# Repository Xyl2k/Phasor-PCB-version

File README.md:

# PHASOR AVR Demo — Custom PCB

This repository contains a custom double-layer PCB design for running the [PHASOR demo](https://www.linusakesson.net/hardware/phasor/index.php) by Linus Åkesson on an ATmega88-20PU microcontroller.

---

## 📁 Contents

- `JSON/`: EasyEDA schematic and board layout plus one 'swapped version' of the RCA connectors 
- `firmware/`: Precompiled HEX file and Flipper Zero-compatible firmware folder
- `enclosure/`: 3D enclosure model (`.stl`)
- `README.md`: Project documentation

---

## ⚙️ Features

- Pure AVR synth demo running on ATmega88  
- Composite PAL video output  
- Generative visuals synced to audio    
- 5V operation (via 78L05 regulator)  
- ISP programming header for flashing

---

## 📦 Bill of Materials (BOM)

| Qty | Component               | Specification           |
|-----|-------------------------|--------------------------|
| x1  | Resistor                | 220 Ω                    |
| x4  | Resistor                | 442 Ω                    |
| x11 | Resistor                | 1 kΩ                     |
| x19 | Resistor                | 2 kΩ                     |
| x3  | Diode                   | 1N4148-35                |
| x2  | Ceramic Capacitor       | 22 pF                    |
| x2  | Electrolytic Capacitor  | 10 µF                    |
| x1  | Header (SPI)            | 2x3                      |
| x1  | Header (Power)          | 1x2                      |
| x1  | LED                     | 3 mm                     |
| x2  | Transistor              | BC547                    |
| x1  | Voltage Regulator       | 78L05                    |
| x1  | IC Socket               | DIP28                    |
| x1  | Microcontroller         | ATmega88-20PU            |
| x1  | Oscillator              | 17.73447 MHz             |
| x2  | RCA Connector           | RCJ-042                  |

> 💡 **Notes:**
> - The **2x3 header** is used for **ISP/SPI programming** of the ATmega88.
> - The **1x2 header** is for **external power supply** (e.g. battery or adapter).

---

## 🔩 Recommended Soldering Order

Follow this order to make the assembly easier and reduce error risk:

1. **🟫 Resistors (220 Ω, 442 Ω, 1 kΩ, 2 kΩ)**  
   Start with the flattest components.

2. **⬛ Diodes (1N4148-35)**  
   Mind the **polarity** (black stripe = cathode).

3. **📎 Ceramic Capacitors (22 pF)**  
   Non-polarized, orientation doesn’t matter.

4. **📦 DIP Socket for ATmega88**  
   Ensure proper orientation with the notch.

5. **⏱️ Oscillator (17.73447 MHz)**  
   Place after flat components are soldered.

6. **⚙️ Transistors (BC547)**  
   Align with the silkscreen (half-moon shape).

7. **💡 LED (3 mm)**  
   ⚠️ Polarity: longer leg = **anode**.

8. **📏 Headers**  
   - **2x3 (SPI)** for programming — solder straight.  
   - **1x2 (Power)** for external power supply.

9. **🔌 Voltage Regulator (78L05)**  
   Check orientation per the silkscreen.

10. **🧯 Electrolytic Capacitors (10 µF)**  
    ⚠️ Respect polarity: longer leg = positive.

11. **🎵 RCA Connectors (RCJ-042)**  
    Large components — solder last to avoid obstruction.

12. **🧠 Microcontroller (ATmega88-20PU)**  
    Insert into the socket, notch facing the same direction as the socket notch.

---

## 🛠️ Flashing the Firmware

The `firmware/` folder includes:

- `flash.hex` — Precompiled firmware for ATmega88-20PU  
- `AVR Flasher/` — Folder structure compatible with **Flipper Zero**

### 🔧 Flashing with Flipper Zero

1. Copy the contents of the `AVR Flasher/` folder to your Flipper Zero's SD card under `/apps_data/avr_isp/`
2. Connect the Flipper to the PHASOR PCB via the **ISP (2x3) header**
3. Launch the **AVR Flasher** app on your Flipper
4. Select `phasor_pcb.avr` and flash it to the ATmega88

---

## ⚠️ Beware: RCA Connector Signal/Ground Inversion

If the RCA connectors are wired incorrectly — with **signal and ground inverted** — the video output will appear **distorted, wavy, or unstable**, even on CRT displays.
Depending of your RCA connector we've included **1-Schematic_Phasor-RCA-Swap.json** and **1-PCB_Phasor-RCA-Swap.json** Who have swapped routes on the RCA, choose the one you need depennding of your connector schematic.

### ✅ Correct RCA wiring:
- **Center pin** = Composite **video signal**
- **Outer ring (shield)** = **Ground**

> 🔧 If your display shows unstable video, check the RCA jack wiring. Inverting signal and ground is a common mistake..

### 💡 Quick Fix:
If you've already soldered the RCA cable and suspect inversion, a quick test is to **cut and reverse the signal and ground wires** on the cable or at the connector.

---

## 🧠 Credits

- **Original demo**: Linus Åkesson  
- **Custom PCB layout**: by me, for my local hackerspace

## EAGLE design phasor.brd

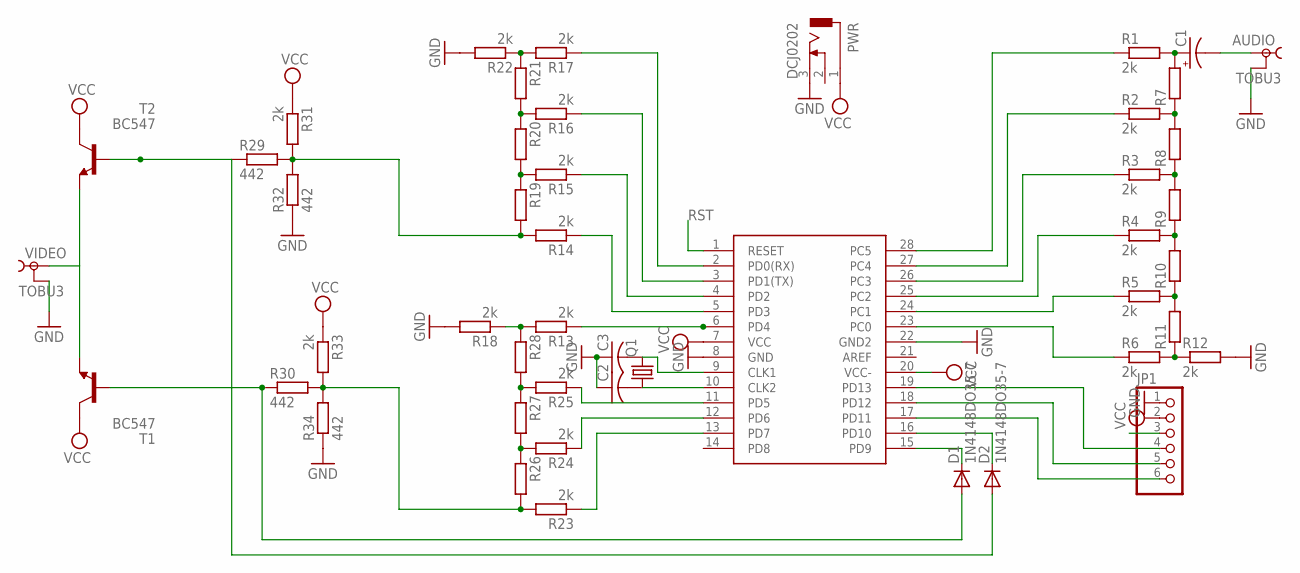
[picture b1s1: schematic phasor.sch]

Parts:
AUDIO: TOBU3
C1: CPOL-USB45181A; B45181A
C2, C3: C-US025-024X044; C025-024X044
D1, D2: 1N4148DO35-7; DO35-7
JP1: PINHD-1X6; 1X06
PWR: DCJ0202
Q1: CRYSTALHC49U70; HC49U70
R1, R2, R3, R4, R5, R6, R12, R13, R14, R15, R16, R17, R18, R22, R23, R24, R25, R31, R33: 2k; 0207/10
R7, R8, R9, R10, R11, R19, R20, R21, R26, R27, R28: R-EU_0204/2V; 0204V
R29: 442; 0204/5
R30, R32, R34: 442; 0204V
T1, T2: BC547; TO92
U$1: 328P; DIL28-3
VIDEO: TOBU3

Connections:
GND: AUDIO.2, AUDIO.2@1 (2), AUDIO.2@2 (2), C2.1, C3.1, JP1.1, PWR.3, R12.2, R18.2, R22.2, R32.1, R34.1, U$1.8 (GND), U$1.22 (GND2), VIDEO.2, VIDEO.2@1 (2), VIDEO.2@2 (2)
unnamed: R1.1, U$1.28 (PC5)
unnamed: R2.1, U$1.27 (PC4)
unnamed: R3.1, U$1.26 (PC3)
unnamed: R4.1, U$1.25 (PC2)
unnamed: R5.1, U$1.24 (PC1)
unnamed: R6.1, U$1.23 (PC0)
unnamed: C1.+, R1.2, R7.2
unnamed: R2.2, R7.1, R8.2
unnamed: R3.2, R8.1, R9.2
unnamed: R4.2, R9.1, R10.2
unnamed: R5.2, R10.1, R11.2
unnamed: R6.2, R11.1, R12.1
unnamed: R17.1, U$1.2 (PD0(RX))
unnamed: R16.1, U$1.3 (PD1(TX))
unnamed: R15.1, U$1.4 (PD2)
unnamed: R14.1, U$1.5 (PD3)
unnamed: R13.1, U$1.6 (PD4)
unnamed: R13.2, R18.1, R28.1
unnamed: R14.2, R19.2, R29.2, R31.2, R32.2
unnamed: R15.2, R19.1, R20.2
unnamed: R16.2, R20.1, R21.2
unnamed: R17.2, R21.1, R22.1
unnamed: R23.2, R26.2, R30.2, R33.2, R34.2
unnamed: R24.2, R26.1, R27.2
unnamed: R25.2, R27.1, R28.2
unnamed: R25.1, U$1.11 (PD5)
unnamed: R24.1, U$1.12 (PD6)
unnamed: R23.1, U$1.13 (PD7)
unnamed: C2.2, Q1.1, U$1.10 (CLK2)
unnamed: C3.2, Q1.2, U$1.9 (CLK1)
unnamed: AUDIO.1, C1.-
unnamed: D1.C, U$1.15 (PD9)
unnamed: D2.C, U$1.16 (PD10)
unnamed: T1.1 (E), T2.1 (E), VIDEO.1
unnamed: D1.A, R30.1, T1.2 (B)
unnamed: D2.A, R29.1, T2.2 (B)
unnamed: JP1.4, U$1.19 (PD13)
unnamed: JP1.5, U$1.18 (PD12)
unnamed: JP1.6, U$1.17 (PD11)
RST: JP1.3, U$1.1 (RESET)
VCC: JP1.2, PWR.1, R31.1, R33.1, T1.3 (C), T2.3 (C), U$1.7 (VCC), U$1.20 (VCC-)

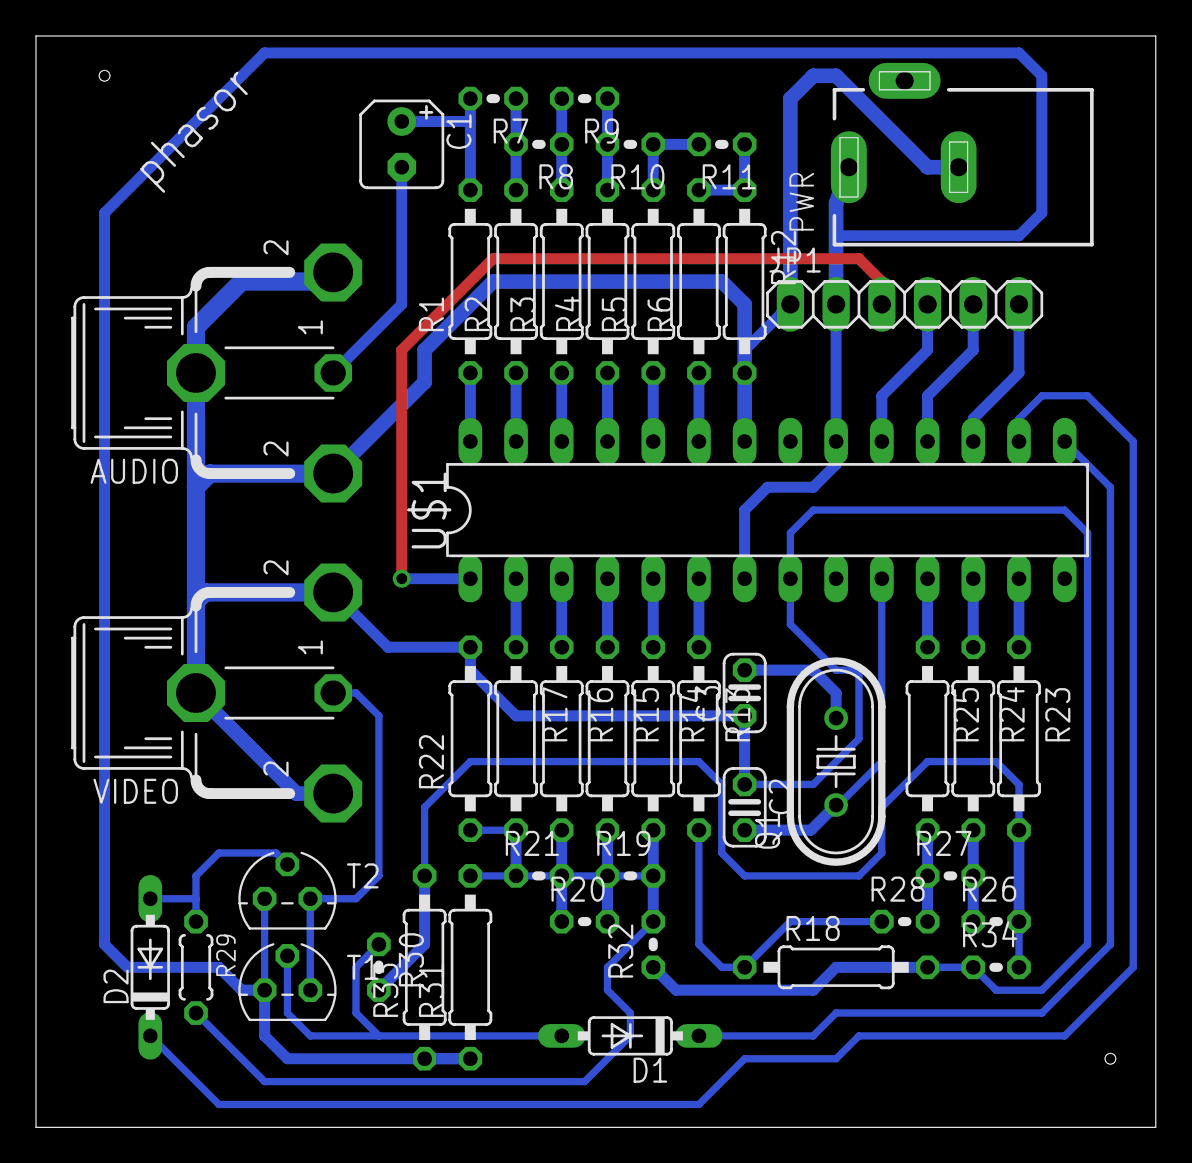
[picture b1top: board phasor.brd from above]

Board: 2 copper layers, 62.2 x 60.6 mm, 47 parts (0 on the bottom side), 42 nets.

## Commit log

2015-03-01 :tada: Added .gitattributes & .gitignore files
2015-03-01 1.0
    1.0
2015-03-01 firmware
    firmware
2025-06-22 Update round
    Update round
2025-06-30 enclosure
    enclosure
2025-07-03 Added swapped rca
    swapped rca routes
